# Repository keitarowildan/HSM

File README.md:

# STM32 Hardware Security Module

## Description
The STM32 Hardware Security Module leverages the STM32F411CEU6 microcontroller along with an SD card module to perform AES-128 encryption and decryption of files. This project uniquely focuses on securely generating and managing cryptographic keys within the STM32 environment, enabling robust encryption and decryption functionalities.

## Installation Instructions
To successfully install and run the STM32 Hardware Security Module, follow these preparatory steps:
1. **Arduino IDE Setup**:
   - Follow the detailed setup instructions for installing the STM32 board package in the Arduino IDE as provided [here](https://www.sgbotic.com/index.php?dispatch=pages.view&page_id=49).

2. **Library Dependencies**:
   - Install the `SdFat` library via the Library Manager to enable operations on the SD card. [SdFat Library on GitHub](https://github.com/greiman/SdFat.git)
   - Install the `AESLib` library to facilitate AES-128 cryptographic operations. [AESLib on GitHub](https://github.com/suculent/thinx-aes-lib.git)

## Hardware Setup
Connect the STM32F411CEU6 to the SD card module as follows:

| SD card module | STM32F411CEU6 |
|----------------|---------------|
| CS             | PB12          |
| SCK            | PB13          |
| MOSI           | PB15          |
| MISO           | PB14          |
| VCC            | 5V/3.3V       |
| GND            | GND           |

## Usage
The module supports several operations through a simple menu-driven interface, accessible via a connected serial monitor:
- **Encrypt**: Encrypt a text inputted to the serial monitor by the user. The encrypted text is stored on the SD card.
- **Decrypt**: Decrypt a ciphertext inputted to the serial monitor.
- **List SD Card Content**: Display a list of files stored on the SD card.
- **Reset**: Reboot the STM32 device, generate a new key, and save the new key inside the SD card.
- **Remove all keys**: Securely delete all cryptographic keys from the SD card.

## Project Status
The project is currently **in development**. Future enhancements will focus on improving security measures, optimizing performance, and expanding the capabilities of file and text handling.

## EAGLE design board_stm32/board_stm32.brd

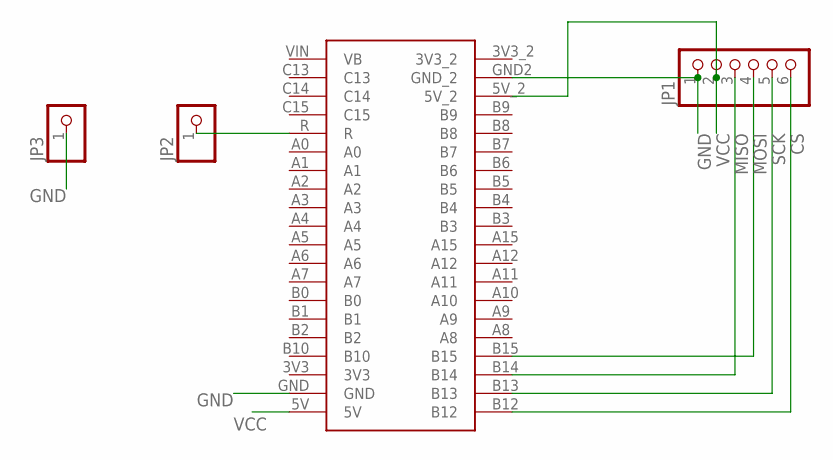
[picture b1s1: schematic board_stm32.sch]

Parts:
JP1: PINHD-1X6; 1X06
JP2, JP3: PINHD-1X1; 1X01
U$1: STM32F411CEU6

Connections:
CS: JP1.6, U$1.B12
GND: JP1.1, JP3.1, U$1.GND, U$1.GND2 (GND_2)
MISO: JP1.3, U$1.B14
MOSI: JP1.4, U$1.B15
unnamed: JP2.1, U$1.R
SCK: JP1.5, U$1.B13
VCC: JP1.2, U$1.5V, U$1.5V_2

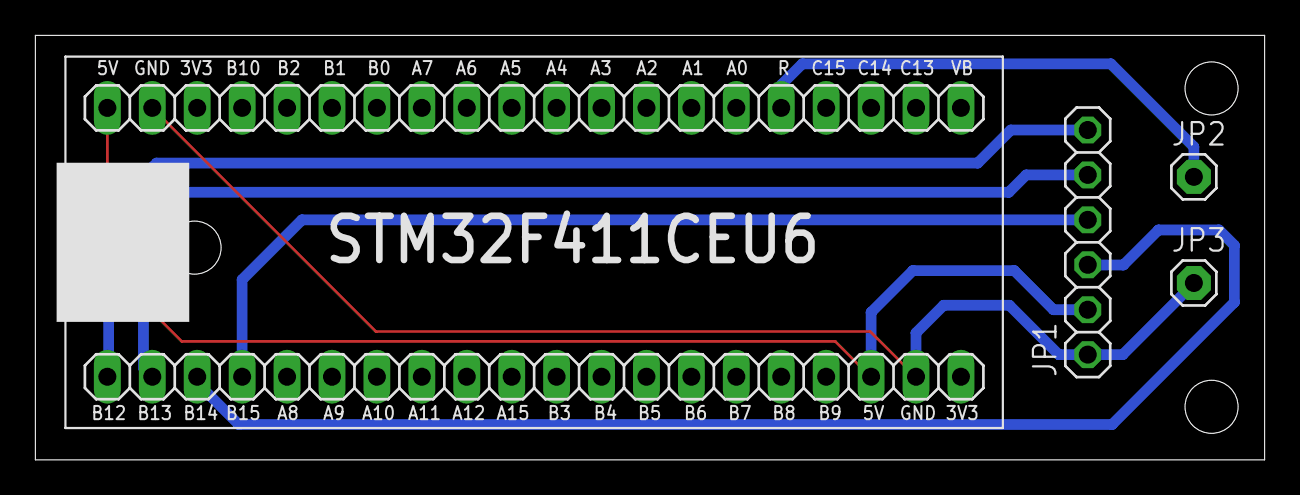
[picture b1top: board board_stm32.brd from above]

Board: 2 copper layers, 69.5 x 24.0 mm, 4 parts (0 on the bottom side), 7 nets.

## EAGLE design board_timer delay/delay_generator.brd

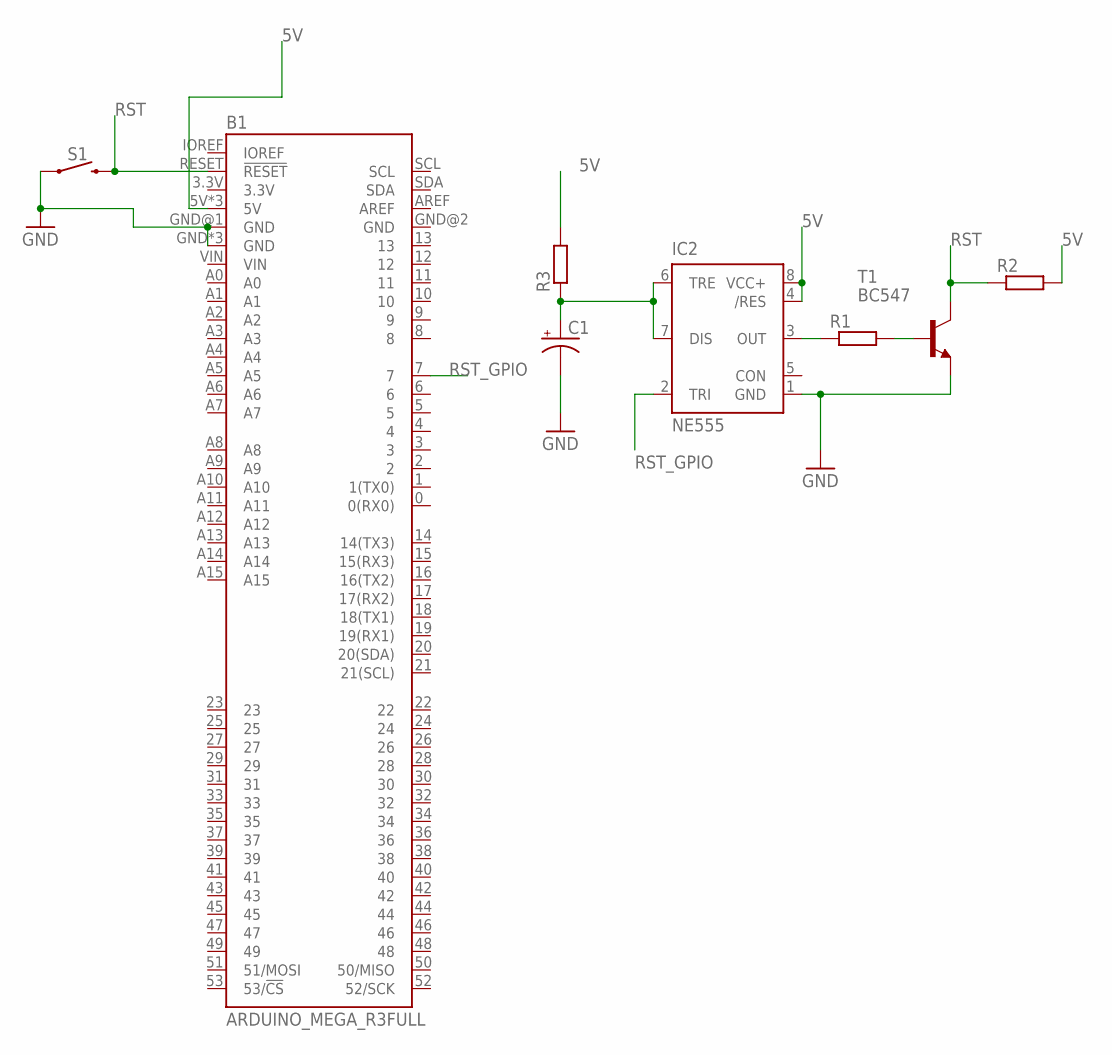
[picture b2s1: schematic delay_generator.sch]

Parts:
B1: ARDUINO_MEGA_R3FULL; ARDUINO_MEGA_NO_SILK
C1: CPOL-USE2.5-6; E2,5-6
IC2: NE555; DIL-08
R1, R2, R3: R-EU_0204/7; 0204/7
S1: MOMENTARY-SWITCH-SPST-PTH-6.0MM; TACTILE_SWITCH_PTH_6.0MM
T1: BC547; TO92

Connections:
5V: B1.5V, B1.5V@1 (5V), B1.5V@2 (5V), IC2.4 (/RES), IC2.8 (VCC+), R2.2, R3.2
GND: B1.GND, B1.GND@1 (GND), B1.GND@3 (GND), B1.GND@4 (GND), C1.-, IC2.1 (GND), S1.1, T1.1 (E)
unnamed: C1.+, IC2.6 (TRE), IC2.7 (DIS), R3.1
unnamed: IC2.3 (OUT), R1.1
unnamed: R1.2, T1.2 (B)
RST: B1.RESET (!RESET), R2.1, S1.3 (2), T1.3 (C)
RST_GPIO: B1.7, IC2.2 (TRI)

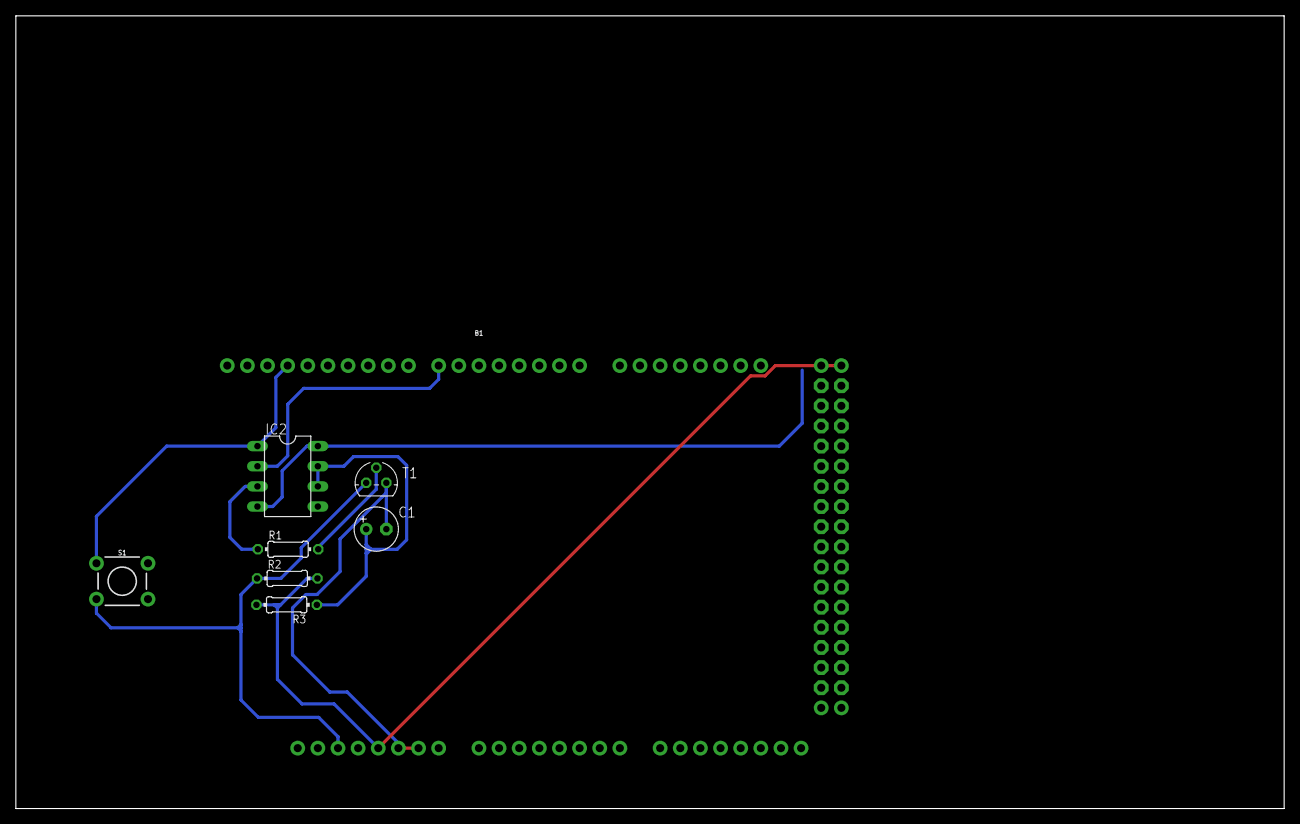
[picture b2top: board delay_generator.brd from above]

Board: 2 copper layers, 160.0 x 100.0 mm, 8 parts (0 on the bottom side), 7 nets.

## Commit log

2024-04-18 inital commit
2024-04-18 encrypt.ino contains both encryption and decryption process
2024-04-18 encrypt.ino generates key and iv randomly
    the decrypted text still stores the previous array, the array isn't cleared out
2024-04-18 reset all arrays in each loop
2024-04-19 base program to decrypt a ciphertext (still doesn't work)
2024-04-19 separate encryption and decryption process (still doesn't work)
2024-04-20 encrypt a file using AESLib (for arduino mega) in STM32 - NOT TESTED
2024-04-22 add base64_iv.ino (examples from AESLib library)
2024-04-22 input plaintext manually from serial monitor
2024-04-23 separate encryption and decryption process
2024-04-23 initial commit: create a program to encrypt and decrypt in one program - STILL NOT WORKING
2024-05-02 add PCB file for STM32
2024-05-02 base64_iv -> base program to enc and dec at one program
2024-05-02 encode and decode in one program
2024-05-03 add process selection step
2024-05-03 randomize key generation
2024-05-03 print the aes key in base64 encoded format
2024-05-07 input key before decrypting
2024-05-08 initial program to utilize iv - DOESNT WORK
2024-05-08 initial commit: utilize eeprom to avoid double use of key
2024-05-10 able to track used keys, key can still be used more than once
2024-05-15 sd_card -> base program to read sd card using sd card module
2024-05-15 new feature: save key to sd card, add option to clear all keys inside the sd card
2024-05-15 remove base64_iv_enc and dec and stm32_crypto
2024-05-15 remove unused variables, functions, and comments
2024-05-16 redesign PCB
2024-05-17 save key and ciphertext to sd card, decrypt ciphertext by inputting file names
2024-05-17 update board
2024-05-21 update gitignore: ignore zip files
2024-05-30 Reorganized folder structure and updated .gitignore

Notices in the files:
parts and their libraries:
SparkFun-Switches: Licensing: Creative Commons ShareAlike 4.0 International - https://creativecommons.org/licenses/by-sa/4.0
